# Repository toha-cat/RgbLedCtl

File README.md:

# RgbLedCtl
RgbLedCtl is an electronic unit and application for controlling RGB led. Communication with the electronic unit is carried out via WiFi.
Based on ESP8266 WiFi SOC with NodeMCU firmware.

The project consists of an electrical unit, lua scripts for ESP8266 and RGBLed -
 control applications.

# Principle of operation
After switching on, the unit is connected to the specified WiFi point. The client (RGBLed) connects to it on the tcp socket. The client sends commands - a color in the form of HEX RGB. The MCU generates the corresponding PWM signals to the keys.

# Electrical scheme
Electrical scheme - project for KiCad. Input power supply 12V. With the help of DC-DK 12v is converted into 5v. whis a linear regulator LM1113 converted 5v to 3.3v. 5v are needed to connect an additional control panel (will be added in the next versions). MOSFETs are used as keys.

# ESP8266 firmware
NodeMCU is used as the firmware. The site of the project http://nodemcu.com/index_en.html. Instructions for the flash firmware https://nodemcu.readthedocs.io/en/master/en/flash/.
After the flash, you need to load lua scripts (from the folder McuScripts) in the MCU. For load scripts recommend using the utility ESPlorer - https://github.com/4refr0nt/ESPlorer.
Before load scripts, rename config.lua.example to config.lua and enter the parameters of your WiFi into it.

# RGBLed
RGBLed - application for control backlight. This is a cross-platform application written using Qt5. The interface is written in QML. The application source code is located in the RGBLed directory as a project for QtCreator.
Qt libraries and theirs source code, as well as QtCreator, can be found on the official Qt website - https://www.qt.io/
Link to the download page Qt5 https://www.qt.io/download-open-source/

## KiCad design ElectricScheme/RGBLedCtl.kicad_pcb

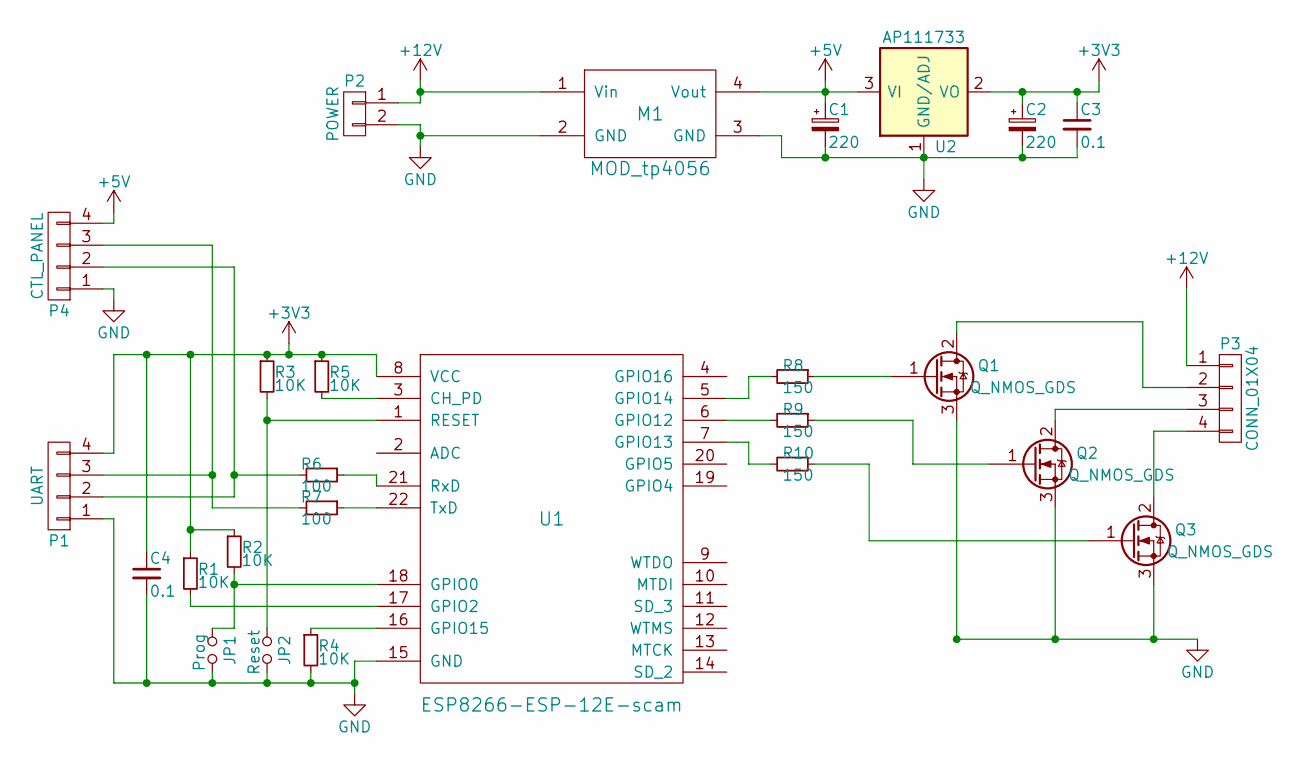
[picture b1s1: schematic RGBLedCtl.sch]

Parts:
C1, C2: 220; C_Radial_D6.3_L11.2_P2.5
C3, C4: 0.1; C_0805_HandSoldering
JP1: Prog; Pin_Header_Straight_1x02
JP2: Reset; SW_PUSH_6mm
M1: MOD_tp4056; DC-DC-mini
P1: UART; Pin_Header_Straight_1x04
P2: POWER; TerminalBlock_Pheonix_PT-3.5mm_2pol
P3: CONN_01X04; TerminalBlock_Pheonix_PT-3.5mm_4pol
P4: CTL_PANEL; Socket_Strip_Straight_1x04
Q1, Q2, Q3: Q_NMOS_GDS; TO-252-2Lead
R1, R2, R3, R4, R5: 10K; R_0805_HandSoldering
R6, R7: 100; R_0805_HandSoldering
R8, R9, R10: 150; R_0805_HandSoldering
U1: ESP8266-ESP-12E-scam; ESP-12E
U2: AP111733; SOT-223

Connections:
+3V3: C2.1, C3.1, C4.1, P1.4, R1.1, R2.1, R3.1, R5.1, U1.8 (VCC), U2.2 (VO), U2.4 (VO)
+5V: C1.1, M1.4 (Vout), P4.4, U2.3 (VI)
+12V: M1.1 (Vin), P2.1, P3.1
GND: C1.2, C2.2, C3.2, C4.2, JP1.2, JP2.2, M1.2 (GND), M1.3 (GND), P1.1, P2.2, P4.1, Q1.3 (S), Q2.3 (S), Q3.3 (S), R4.2, U1.15 (GND), U2.1 (GND/ADJ)
unnamed: JP1.1, R2.2, U1.18 (GPIO0)
unnamed: JP2.1, R3.2, U1.1 (RESET)
unnamed: P1.2, P4.2, R6.2
unnamed: P1.3, P4.3, R7.2
unnamed: P3.2, Q1.2 (D)
unnamed: P3.3, Q2.2 (D)
unnamed: P3.4, Q3.2 (D)
unnamed: Q1.1 (G), R8.1
unnamed: Q2.1 (G), R9.1
unnamed: Q3.1 (G), R10.1
unnamed: R1.2, U1.17 (GPIO2)
unnamed: R4.1, U1.16 (GPIO15)
unnamed: R5.2, U1.3 (CH_PD)
unnamed: R6.1, U1.21 (RxD)
unnamed: R7.1, U1.22 (TxD)
unnamed: R8.2, U1.5 (GPIO14)
unnamed: R9.2, U1.6 (GPIO12)
unnamed: R10.2, U1.7 (GPIO13)

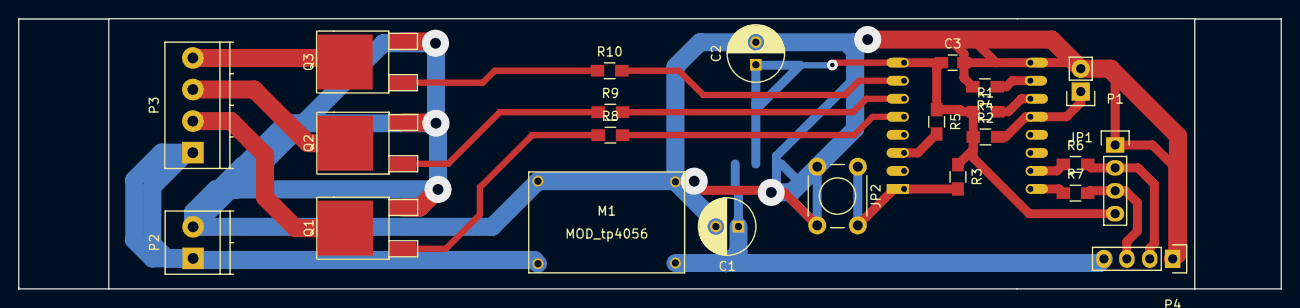
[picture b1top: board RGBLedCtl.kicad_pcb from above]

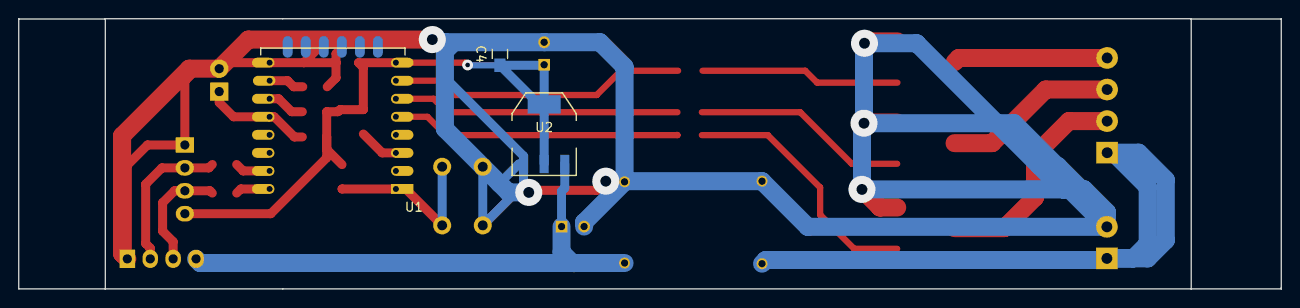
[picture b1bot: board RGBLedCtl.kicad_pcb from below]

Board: 2 copper layers, 140.0 x 30.0 mm, 26 parts (3 on the bottom side), 22 nets.

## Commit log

2017-05-14 create project
2017-05-14 add description end edit gitignore
